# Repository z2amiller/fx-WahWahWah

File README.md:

# fx-WahWahWah — Thomas Organ Cry-Baby (95-910511) reproduction PCB

An open-hardware KiCad recreation of the 1970s Thomas Organ Cry-Baby wah,
model **95-910511**, board **25-5500-2**.

The goal is a modern two-layer board that drops into an original Thomas Organ
shell and accepts either vintage or modern parts — including the original TDK
5103 "cube" inductor, the earlier round "stack of dimes" inductor, or a current
production replacement.

> **Status: not yet fabricated.** The design passes electrical and clearance
> checks (see [Verification](#verification)) but no board has been made or
> tested. Dimensions carry the tolerances documented below. If you build one,
> please open an issue and say how it went.

---

## Design goals

1. **Drop into an original shell.** Mounting features match the original board
   so it fits a period Thomas Organ chassis.
2. **Take any inductor.** One land pattern accepts modern two-lead wah
   inductors *and* both vintage four-post types.
3. **Vintage or modern passives.** Every resistor and capacitor has two
   footprints — one sized for 1970s carbon-comp and film parts, one for modern
   components — so builders choose the look they want.
4. **Hand-built.** Through-hole throughout, no assembly service required.

---

## Board

| | |
|---|---|
| Size | 3.000 × 2.0625 in (76.20 × 52.39 mm) |
| Layers | 2 |
| Mounting | 2 round holes + 1 edge slot |

### Mounting geometry

Origin at the **top-left corner**, component side up, X right / Y down —
the orientation of the original etch artwork.

| Feature | X (mm) | Y (mm) | Tolerance |
|---|---|---|---|
| Edge slot (left) | 3.05 | 9.97 | ±1.0 mm |
| Right hole | 70.36 | 24.87 | ±0.5 mm |
| Bottom hole | 50.22 | 44.82 | ±0.6 mm |

The left feature is cut as an **open slot in `Edge.Cuts`**, not a drilled hole.
On original boards this position is a hole that has broken out through the
board edge — the remaining web is only ~1.3 mm and cracks under a torqued
screw. Cutting it open avoids reproducing that failure, and because the slot
is open the ±1.0 mm X tolerance stops mattering.

Holes are oversized relative to stock to absorb the tolerances above. Screws
are #6 pan head (~6.4 mm head), which is the limit on how far they can be
opened up.

---

## Circuit

Standard Cry-Baby topology, transcribed from the period schematic:

- **Q1** — common-emitter gain stage, biased by an R6/R5 (470K/100K) divider
  tapped off its own collector, fed back to the base through the inductor
  network and R3 (1.5K).
- **Wah pot** takes Q1's collector through C4 and feeds its wiper to **Q2**.
- **Q2** — emitter follower driving the L/C tank through C3.
- **Tank** — L1 (500 mH) in parallel with R4 (33K) for damping; the resonant
  peak sweeps with the pot, and the loop closes back at Q1's base.

Bias is tolerant of transistor gain: across hFE 235 → 1200, Q1's collector
current moves only ~6% and Vc stays near mid-rail. **hFE is a voicing choice,
not a bias constraint** — it sets loop gain, so it controls how sharp and vocal
the peak is. The original specified 235–470 hFE; higher-gain parts give a
peakier, more aggressive wah.

---

## Bill of materials

Resistors `R1`–`R10` and capacitors `C1`–`C5` are the **modern** footprints.
`R21`–`R30` and `C21`–`C25` are the **vintage-sized** alternates at the same
positions, marked DNP.

| Ref | Value | Ref | Value |
|---|---|---|---|
| R1 | 68K | C1 | 10n |
| R2 | 470R | C2 | 4.7µ (see note) |
| R3 | 1.5K | C3 | 10n |
| R4 | 33K | C4 | 220n |
| R5 | 100K | C5 | 220n |
| R6 | 470K | L1 | 500 mH |
| R7 | 22K | Q1 | 2N5088 |
| R8 | 470K | Q2 | 2N5089 |
| R9 | 10K | RV1 | 100K log (off-board) |
| R10 | 1K | SW1 | SPDT (off-board) |

**Populate one variant per position, not both.** The footprints deliberately
overlap.

*C2 note:* the original is 3.9 µF, which is effectively unobtainable today.
The modern position is 4.7 µF; the vintage alternate (C22) keeps 3.9 µF. 
Several alternate footprints are added here - The 2mm lead offset
footprint fits modern electrolytics, there's a 5mm offset footprint that
will fit most tantalum caps, and the original ~15mm offset to fit a radial
cap or as on many older boards, a tantalum with the leads bent out.

In addition, there is an alternate landing for C2 in the upper right of
the board that can be populated by 2 2.2uF film box capacitors. These
retain the audio transparency of tantalum caps while still being
in production today (despite being a bit expensive).

Only populate one of these landings - either one of the footprints
below the inductor, or the pair of film caps in the upper right side
of the board.

### Passive lead pitches

Vintage footprints use the original board's spacings:

| Span | Pitch | Used by |
|---|---|---|
| 2× | 0.53 in / 13.5 mm | carbon-comp resistors |
| 3× | 0.80 in / 20.3 mm | 0.01 µF film caps |
| 4× | 1.06 in / 27.0 mm | 0.22 µF film caps |

The original was hand-taped on a ~0.265 × 0.1665 in grid — **not** a clean
decimal grid. Don't try to force these to 0.1 in increments.

### Transistors

The original board's silkscreen reads **E-C-B for Q1 and B-C-E for Q2** —
mirrored, and matching no modern part. This board uses **E-B-C** throughout and
silkscreens the pin letters rather than relying on the package outline, so any
part goes in whichever way puts its emitter on the E pad.

BC549/BC550 (C-B-E) also drop straight in — base is centre on both pinouts, so
they simply insert rotated 180°. If you want the stock voicing, **BC549B**
(hFE 200–450) brackets the original 235–470 spec more closely than either
2N5088 (300–900) or 2N5089 (400–1200).

---

## Inductor

`L1` uses a custom universal land pattern (`Wah_Inductor_Universal`, in
`fx-WahWahWah.pretty/`):

- **Four radial runways, three holes each.** Opposing pairs give lead spacings
  of **10.8 / 12.6 / 14.4 / 16.2 / 18.0 mm**. The 14.4 mm option matches the
  [stompboxparts ME-6](https://stompboxparts.com/transformers-inductors/wah-inductor-me-6/)
  (570 mH, 40 Ω max, Allied ARM6-4102-A) exactly.
- **A 14.85 × 12.29 mm four-post rectangle** for the original TDK 5103 cube and
  the earlier stack-of-dimes. Both vintage inductors share this pattern.

On the vintage rectangle, only the **left pair is electrical**; the right pair
is mechanical and carries no net. This matches the original artwork, where only
the left two posts had traces — if the 5103's right-hand posts are shield or
case tabs, netting them would short the coil to the can.

All same-numbered holes are tied together in copper, so whichever pair a
builder populates is live.

---

## Off-board wiring

The board carries no output pad — this is correct and matches the original.
The output jack is fed from the switch entirely off-board, and the wah signal
reaches the switch via the LUG 3 node.

| Pin | Net | Goes to |
|---|---|---|
| 1 | POT_LUG_2 | Wah pot, lug 2 (wiper) |
| 2, 3 | IN_JACK_TIP | Input jack tip; SPDT switch |
| 4 | POT_LUG_3 | Wah pot, lug 3 |
| 5, 6 | BATT_NEG | Battery −; input jack ring |
| 7 | +9V | Battery + |
| 8 | GND | Input jack sleeve |
| 9, 10 | GND | Spare grounds |

Battery negative returns through the input jack ring, so inserting a plug
powers the circuit — the stock arrangement.

### Grounding notes

- **Do not ground the mounting screws.** The shell is already at circuit ground
  through the jack bushings; bonding it again through the screws adds redundant
  paths that carry no return current and invites ground loops.
- **Do run a wire to pot lug 1.** It's the bottom of the divider that sets loop
  gain, and in the stock wiring its only return is through the enclosure
  casting. Use one of the spare ground pads (J1.9/J1.10) rather than relying on
  50-year-old bushing continuity — a corroded joint there makes the sweep
  scratchy and weak.

---

## Verification

Checked against JLCPCB's published constraints:

| Check | Result | Limit |
|---|---|---|
| Hole-to-hole, 92 through-holes | 0 violations | 0.5 mm |
| Different-net copper | min 0.800 mm | — |
| Copper to board edge / cutouts | min 0.500 mm | 0.2 mm |
| Non-plated slot width | 4.5 mm | 1.0 mm |

**DRC shows courtyard overlaps.** These are expected and intentional: the
vintage and modern footprints occupy the same positions by design, and only one
is ever populated. Courtyards are a pick-and-place abstraction and carry no
fabrication or electrical meaning on a hand-built board. Every check that maps
to a physical constraint passes.

---

## Provenance and tolerances

No original board was available to measure directly. The dimensions here were
derived photogrammetrically from published references and cross-validated
between independent sources:

1. A hobbyist home-etching layout sheet (dimensional reference only).
2. A photograph of a populated original board, perspective-corrected via
   homography against the stated 3.000 × 2.0625 in outline.
3. A photograph of a second unit of a different revision, used to confirm that
   hole positions are constant across revisions.

Sources 1 and 2 agree on hole-to-hole vectors to **0.47–1.57 mm**, with a
best-fit scale ratio of 0.9925. Sources 2 and 3 agree to within **1.04 mm** —
the noise floor of the photographs — confirming that the hole pattern did not
change between board revisions.

**If you have an original board and calipers, measurements would be very
welcome.** The two round mounting holes and the inductor rectangle are the
numbers most worth confirming.

---

## Credits

- **[Vintage Cry-Baby thread on the PedalPCB forum](https://forum.pedalpcb.com/threads/vintage-cry-baby.29962/)**
  — the discussion that started this, and the source of the reference material.
- **Andrew F. Shorty** — the schematic transcription and home-etching layout
  that served as the dimensional reference.
- **Forum members** who photographed original hardware, without which none of
  the measurements would have been possible.
- **PedalPCB** — the [Tear Jerker Wah](https://docs.pedalpcb.com/project/TearJerker.pdf)
  build documentation, whose universal inductor land pattern informed the
  runway geometry here.

Reference documents are **not** redistributed in this repository; they remain
the property of their respective authors. Follow the links above for the
originals.

---

## License

Licensed under the **CERN Open Hardware Licence Version 2 – Permissive**
(CERN-OHL-P v2). See [LICENSE](LICENSE) and [NOTICE](NOTICE).

You may make, modify, and sell boards from these files, with no obligation to
publish your changes. The underlying circuit dates from the 1970s and its
patents have long since expired.

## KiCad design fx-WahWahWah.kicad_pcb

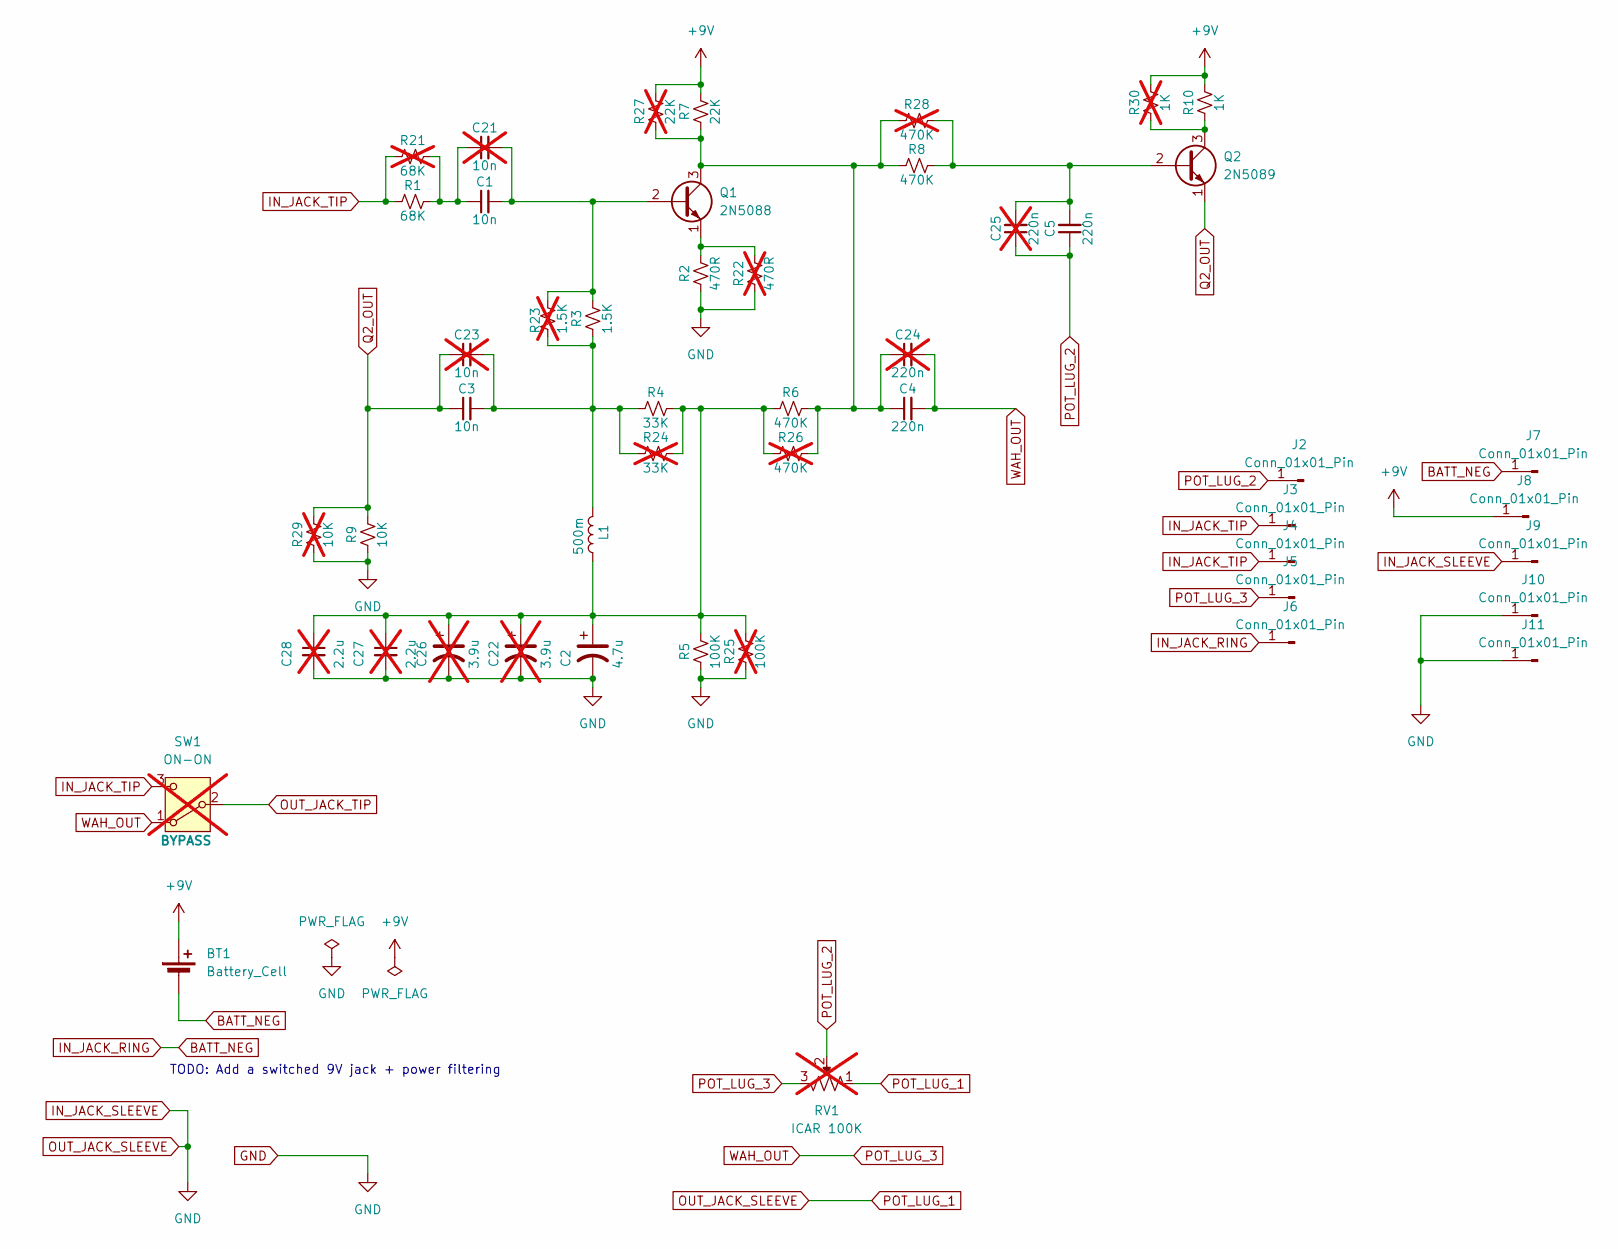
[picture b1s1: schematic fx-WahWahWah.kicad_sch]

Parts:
BT1: Battery_Cell
C1, C3: 10n; C_Rect_L7.2mm_W2.5mm_P5.00mm_FKS2_FKP2_MKS2_MKP2
C2: 4.7u; CP_Radial_D4.0mm_P2.00mm
C4, C5: 220n; C_Rect_L7.2mm_W2.5mm_P5.00mm_FKS2_FKP2_MKS2_MKP2
C21, C23: 10n; C_Rect_L16.5mm_W4.7mm_P15.00mm_MKT; not fitted
C22: 3.9u; C_Rect_L16.5mm_W4.7mm_P15.00mm_MKT; not fitted
C24, C25: 220n; C_Rect_L16.5mm_W4.9mm_P15.00mm_MKT; not fitted
C26: 3.9u; C_Rect_L7.2mm_W4.5mm_P5.00mm_FKS2_FKP2_MKS2_MKP2; not fitted
C27, C28: 2.2u; C_Rect_L7.2mm_W7.2mm_P5.00mm; not fitted
J2, J3, J4, J5, J6, J7, J8, J9, J10, J11: Conn_01x01_Pin; Vector T46-5-9M
L1: 500m; Wah_Inductor_Universal
Q1: 2N5088; TO-92L_Inline_Wide
Q2: 2N5089; TO-92L_Inline_Wide
R1: 68K; R_Axial_DIN0204_L3.6mm_D1.6mm_P7.62mm_Horizontal
R2: 470R; R_Axial_DIN0204_L3.6mm_D1.6mm_P7.62mm_Horizontal
R3: 1.5K; R_Axial_DIN0204_L3.6mm_D1.6mm_P7.62mm_Horizontal
R4: 33K; R_Axial_DIN0204_L3.6mm_D1.6mm_P7.62mm_Horizontal
R5: 100K; R_Axial_DIN0204_L3.6mm_D1.6mm_P7.62mm_Horizontal
R6, R8: 470K; R_Axial_DIN0204_L3.6mm_D1.6mm_P7.62mm_Horizontal
R7: 22K; R_Axial_DIN0204_L3.6mm_D1.6mm_P7.62mm_Horizontal
R9: 10K; R_Axial_DIN0204_L3.6mm_D1.6mm_P7.62mm_Horizontal
R10: 1K; R_Axial_DIN0204_L3.6mm_D1.6mm_P7.62mm_Horizontal
R21: 68K; R_Axial_DIN0411_L9.9mm_D3.6mm_P15.24mm_Horizontal; not fitted
R22: 470R; R_Axial_DIN0411_L9.9mm_D3.6mm_P15.24mm_Horizontal; not fitted
R23: 1.5K; R_Axial_DIN0411_L9.9mm_D3.6mm_P15.24mm_Horizontal; not fitted
R24: 33K; R_Axial_DIN0411_L9.9mm_D3.6mm_P15.24mm_Horizontal; not fitted
R25: 100K; R_Axial_DIN0411_L9.9mm_D3.6mm_P15.24mm_Horizontal; not fitted
R26, R28: 470K; R_Axial_DIN0411_L9.9mm_D3.6mm_P15.24mm_Horizontal; not fitted
R27: 22K; R_Axial_DIN0411_L9.9mm_D3.6mm_P15.24mm_Horizontal; not fitted
R29: 10K; R_Axial_DIN0411_L9.9mm_D3.6mm_P15.24mm_Horizontal; not fitted
R30: 1K; R_Axial_DIN0411_L9.9mm_D3.6mm_P15.24mm_Horizontal; not fitted
RV1: ICAR 100K; not fitted
SW1: ON-ON; not fitted

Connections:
+9V: BT1.1 (+), J8.1 (Pin_1_1), R7.2, R10.2, R27.2, R30.2
BATT_NEG: BT1.2 (-), J6.1 (Pin_1_1), J7.1 (Pin_1_1)
GND: C2.2, C22.2, C26.2, C27.2, C28.2, J9.1 (Pin_1_1), J10.1 (Pin_1_1), J11.1 (Pin_1_1), R2.1, R5.1, R9.1, R22.1, R25.1, R29.1, RV1.1
IN_JACK_TIP: J3.1 (Pin_1_1), J4.1 (Pin_1_1), R1.1, R21.1, SW1.3 (C)
unnamed: C1.1, C21.1, R1.2, R21.2
unnamed: C2.1, C22.1, C26.1, C27.1, C28.1, L1.1, R4.2, R5.2, R6.1, R24.2, R25.2, R26.1
unnamed: C3.2, C23.2, L1.2, R3.1, R4.1, R23.1, R24.1
unnamed: C1.2, C21.2, Q1.2 (B), R3.2, R23.2
unnamed: C4.1, C24.1, Q1.3 (C), R6.2, R7.1, R8.1, R26.2, R27.1, R28.1
unnamed: Q1.1 (E), R2.2, R22.2
unnamed: C5.2, C25.2, Q2.2 (B), R8.2, R28.2
unnamed: Q2.3 (C), R10.1, R30.1
POT_LUG_2: C5.1, C25.1, J2.1 (Pin_1_1), RV1.2
POT_LUG_3: C4.2, C24.2, J5.1 (Pin_1_1), RV1.3, SW1.1 (A)
Q2_OUT: C3.1, C23.1, Q2.1 (E), R9.2, R29.2

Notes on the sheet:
TODO: Add a switched 9V jack + power filtering

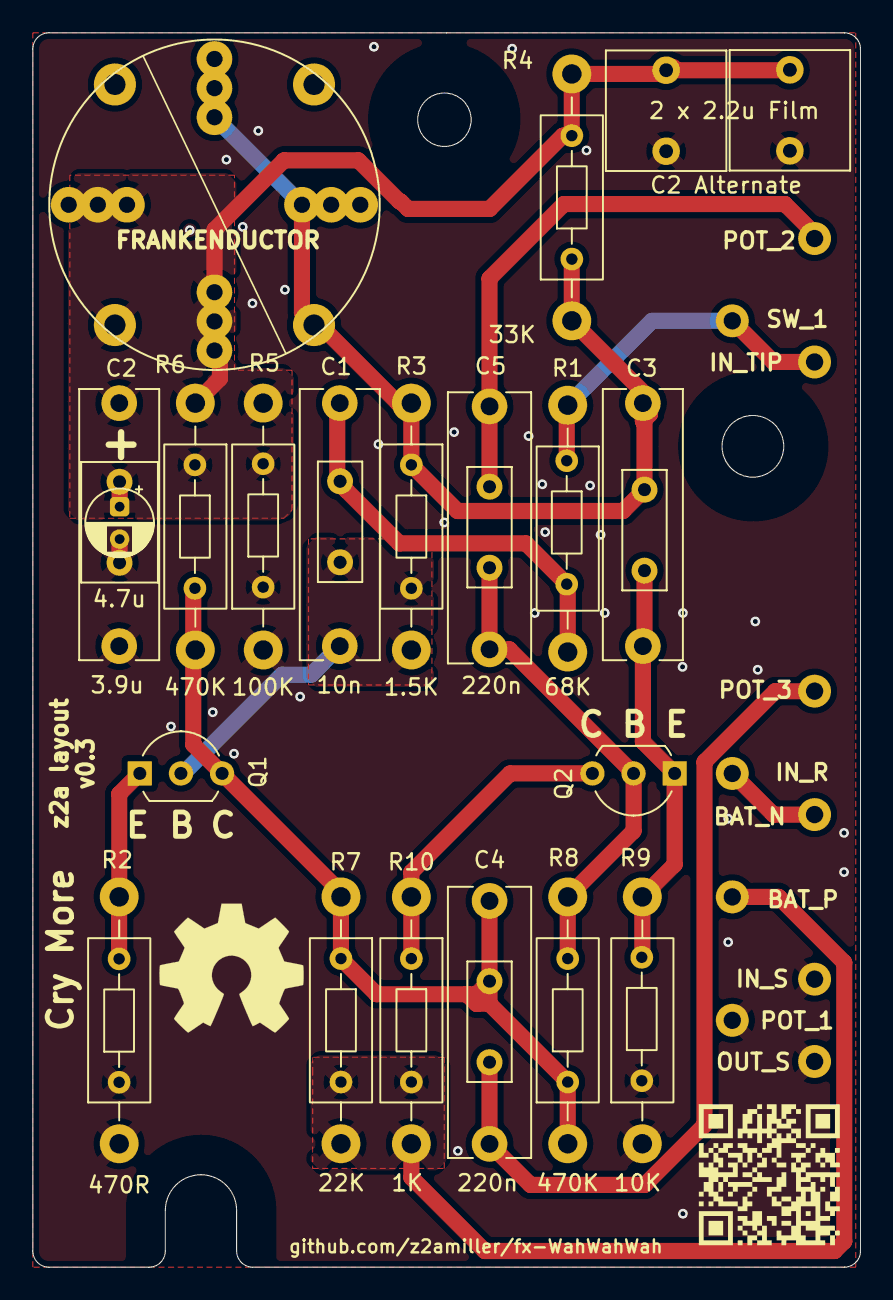
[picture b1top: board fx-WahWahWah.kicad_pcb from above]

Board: 2 copper layers, 51.1 x 76.2 mm, 47 parts (0 on the bottom side), 15 nets.

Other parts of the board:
QR*****: fx-WahWahWah-repo
